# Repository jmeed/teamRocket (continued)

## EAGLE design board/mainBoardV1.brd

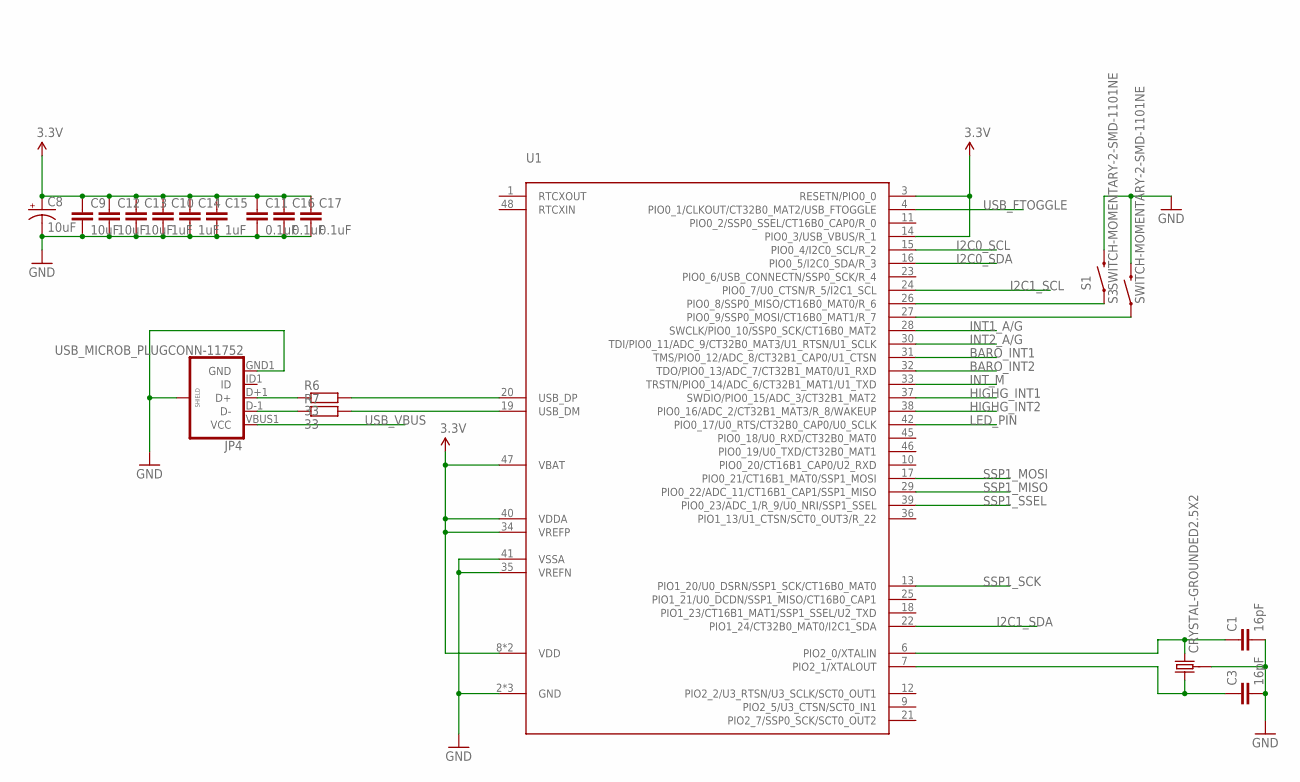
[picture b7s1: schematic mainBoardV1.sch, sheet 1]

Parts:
C1, C3: 16pF; C0402
C8: 10uF; CT3216
C9, C12, C13: 10uF; C0402
C10, C14, C15: 1uF; C0402
C11, C16, C17: 0.1uF; C0402
JP4: USB_MICROB_PLUGCONN-11752; USB-B-MICRO-SMD_V03
R6, R7: 33; R0402
S1, S3: SWITCH-MOMENTARY-2-SMD-1101NE; TACTILE-SWITCH-1101NE
U1: LPC11U68JBD48; LQFP48
U$5: CRYSTAL-GROUNDED2.5X2; CRYSTAL-SMD-2.5X2

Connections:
3.3V: C8.A (+), C9.1, C10.1, C11.1, C12.1, C13.1, C14.1, C15.1, C16.1, C17.1, U1.3 (RESETN/PIO0_0), U1.8 (VDD), U1.14 (PIO0_3/USB_VBUS/R_1), U1.34 (VREFP), U1.40 (VDDA), U1.44 (VDD), U1.47 (VBAT); also elsewhere on the board
BARO_INT1: U1.31 (TMS/PIO0_12/ADC_8/CT32B1_CAP0/U1_CTSN); also elsewhere on the board
BARO_INT2: U1.32 (TDO/PIO0_13/ADC_7/CT32B1_MAT0/U1_RXD); also elsewhere on the board
GND: C1.2, C3.2, C8.C (-), C9.2, C10.2, C11.2, C12.2, C13.2, C14.2, C15.2, C16.2, C17.2, JP4.GND1 (GND), JP4.SHIELD1 (SHIELD), JP4.SHIELD2 (SHIELD), JP4.SHIELD3 (SHIELD), S1.2, S3.2, U1.2 (GND), U1.5 (GND), U1.35 (VREFN), U1.41 (VSSA), U1.43 (GND), U$5.GND1 (3), U$5.GND2 (3); also elsewhere on the board
HIGHG_INT1: U1.37 (SWDIO/PIO0_15/ADC_3/CT32B1_MAT2); also elsewhere on the board
HIGHG_INT2: U1.38 (PIO0_16/ADC_2/CT32B1_MAT3/R_8/WAKEUP); also elsewhere on the board
I2C0_SCL: U1.15 (PIO0_4/I2C0_SCL/R_2); also elsewhere on the board
I2C0_SDA: U1.16 (PIO0_5/I2C0_SDA/R_3); also elsewhere on the board
I2C1_SCL: U1.24 (PIO0_7/U0_CTSN/R_5/I2C1_SCL); also elsewhere on the board
I2C1_SDA: U1.22 (PIO1_24/CT32B0_MAT0/I2C1_SDA); also elsewhere on the board
INT1_A/G: U1.28 (SWCLK/PIO0_10/SSP0_SCK/CT16B0_MAT2); also elsewhere on the board
INT2_A/G: U1.30 (TDI/PIO0_11/ADC_9/CT32B0_MAT3/U1_RTSN/U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); also elsewhere on the board
INT_M: U1.33 (TRSTN/PIO0_14/ADC_6/CT32B1_MAT1/U1_TXD); also elsewhere on the board
LED_PIN: U1.42 (PIO0_17/U0_RTS/CT32B0_CAP0/U0_SCLK); also elsewhere on the board
unnamed: C3.1, U1.7 (PIO2_1/XTALOUT), U$5.P1 (1)
unnamed: C1.1, U1.6 (PIO2_0/XTALIN), U$5.P2 (2)
unnamed: R6.2, U1.20 (USB_DP)
unnamed: JP4.D+1 (D+), R6.1
unnamed: JP4.D-1 (D-), R7.1
unnamed: R7.2, U1.19 (USB_DM)
unnamed: S3.1, U1.27 (PIO0_9/SSP0_MOSI/CT16B0_MAT1/R_7)
unnamed: S1.1, U1.26 (PIO0_8/SSP0_MISO/CT16B0_MAT0/R_6)
SSP1_MISO: U1.29 (PIO0_22/ADC_11/CT16B1_CAP1/SSP1_MISO); also elsewhere on the board
SSP1_MOSI: U1.17 (PIO0_21/CT16B1_MAT0/SSP1_MOSI); also elsewhere on the board
SSP1_SCK: U1.13 (PIO1_20/U0_DSRN/SSP1_SCK/CT16B0_MAT0); also elsewhere on the board
SSP1_SSEL: U1.39 (PIO0_23/ADC_1/R_9/U0_NRI/SSP1_SSEL); also elsewhere on the board
USB_FTOGGLE: U1.4 (PIO0_1/CLKOUT/CT32B0_MAT2/USB_FTOGGLE); also elsewhere on the board
USB_VBUS: JP4.VBUS1 (VCC); also elsewhere on the board

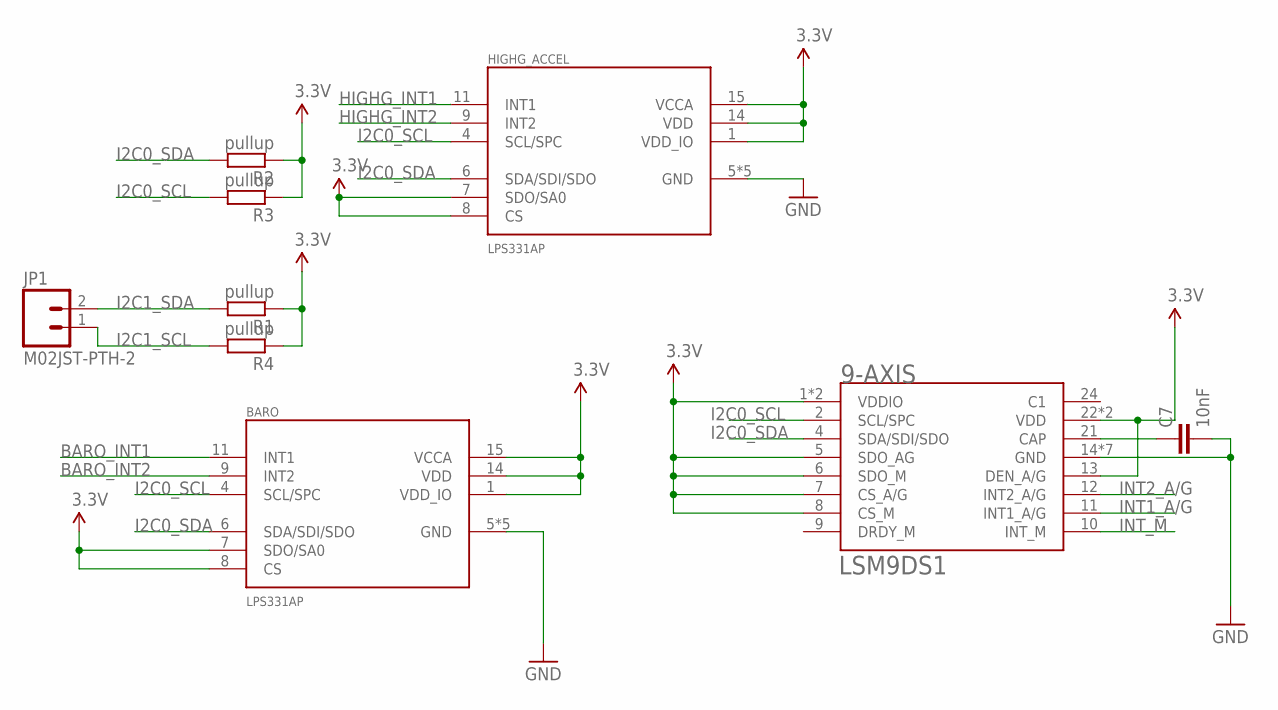
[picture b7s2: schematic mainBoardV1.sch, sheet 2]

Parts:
9-AXIS: LSM9DS1; LGA-24L-3.5X3X1
BARO: LPS331AP; LGA-16-3X3X1
C7: 10nF; C0402
HIGHG_ACCEL: LPS331AP; LGA-16-3X3X1
JP1: M02JST-PTH-2; JST-2-PTH
R1, R2, R3, R4: pullup; R0402

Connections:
3.3V: 9-AXIS.1 (VDDIO), 9-AXIS.3 (VDDIO), 9-AXIS.5 (SDO_AG), 9-AXIS.6 (SDO_M), 9-AXIS.7 (CS_A/G), 9-AXIS.8 (CS_M), 9-AXIS.13 (DEN_A/G), 9-AXIS.22 (VDD), 9-AXIS.23 (VDD), BARO.1 (VDD_IO), BARO.7 (SDO/SA0), BARO.8 (CS), BARO.14 (VDD), BARO.15 (VCCA), HIGHG_ACCEL.1 (VDD_IO), HIGHG_ACCEL.7 (SDO/SA0), HIGHG_ACCEL.8 (CS), HIGHG_ACCEL.14 (VDD), HIGHG_ACCEL.15 (VCCA), R1.1, R2.1, R3.1, R4.1; also elsewhere on the board
BARO_INT1: BARO.11 (INT1); also elsewhere on the board
BARO_INT2: BARO.9 (INT2); also elsewhere on the board
GND: 9-AXIS.14 (GND), 9-AXIS.15 (GND), 9-AXIS.16 (GND), 9-AXIS.17 (GND), 9-AXIS.18 (GND), 9-AXIS.19 (GND), 9-AXIS.20 (GND), BARO.5 (GND), BARO.10 (GND), BARO.12 (GND), BARO.13 (GND), BARO.16 (GND), C7.2, HIGHG_ACCEL.5 (GND), HIGHG_ACCEL.10 (GND), HIGHG_ACCEL.12 (GND), HIGHG_ACCEL.13 (GND), HIGHG_ACCEL.16 (GND); also elsewhere on the board
HIGHG_INT1: HIGHG_ACCEL.11 (INT1); also elsewhere on the board
HIGHG_INT2: HIGHG_ACCEL.9 (INT2); also elsewhere on the board
I2C0_SCL: 9-AXIS.2 (SCL/SPC), BARO.4 (SCL/SPC), HIGHG_ACCEL.4 (SCL/SPC), R3.2; also elsewhere on the board
I2C0_SDA: 9-AXIS.4 (SDA/SDI/SDO), BARO.6 (SDA/SDI/SDO), HIGHG_ACCEL.6 (SDA/SDI/SDO), R2.2; also elsewhere on the board
I2C1_SCL: JP1.1, R4.2; also elsewhere on the board
I2C1_SDA: JP1.2, R1.2; also elsewhere on the board
INT1_A/G: 9-AXIS.11 (INT1_A/G); also elsewhere on the board
INT2_A/G: 9-AXIS.12 (INT2_A/G); also elsewhere on the board
INT_M: 9-AXIS.10 (INT_M); also elsewhere on the board
unnamed: 9-AXIS.21 (CAP), C7.1

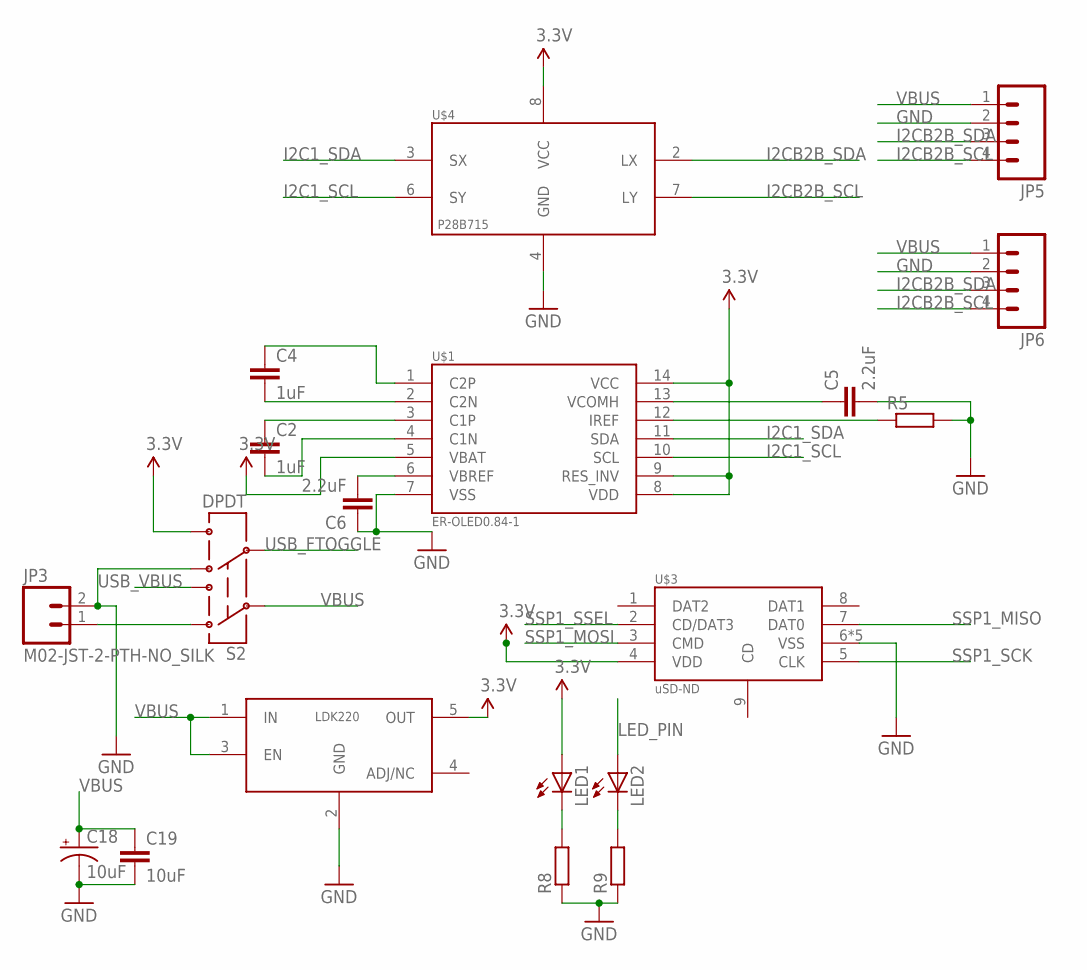
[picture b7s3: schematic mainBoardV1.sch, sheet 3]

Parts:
C2, C4: 1uF; C0402
C5, C6: 2.2uF; C0402
C18: 10uF; CT3216
C19: 10uF; C0402
JP3: M02-JST-2-PTH-NO_SILK; JST-2-PTH-NS
JP5, JP6: M04JST; 1X04-1.5MM_JST
LED1, LED2: LEDCHIPLED_0603; CHIPLED_0603
R5, R8, R9: R0402
S2: DPDT; AYZ0202
U$1: ER-OLED0.84-1; MOLEX_52892-1433
U$2: LDK220M33R; SOT23-5
U$3: MICROSD-CD; MOLEX_SD-47352-101
U$4: P82B715; SO8

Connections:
3.3V: LED1.A, S2.6, U$1.5 (VBAT), U$1.8 (VDD), U$1.9 (RES_INV), U$1.14 (VCC), U$2.5 (OUT), U$3.4 (VDD), U$4.8 (VCC); also elsewhere on the board
GND: C5.2, C6.1, C18.C (-), C19.2, JP3.2, JP5.2, JP6.2, R5.2, R8.1, R9.1, S2.4, U$1.7 (VSS), U$2.2 (GND), U$3.6 (VSS), U$3.G1 (VSS), U$3.G2 (VSS), U$3.G3 (VSS), U$3.G4 (VSS), U$4.4 (GND); also elsewhere on the board
I2C1_SCL: U$1.10 (SCL), U$4.6 (SY); also elsewhere on the board
I2C1_SDA: U$1.11 (SDA), U$4.3 (SX); also elsewhere on the board
I2CB2B_SCL: JP5.4, JP6.4, U$4.7 (LY)
I2CB2B_SDA: JP5.3, JP6.3, U$4.2 (LX)
LED_PIN: LED2.A; also elsewhere on the board
unnamed: JP3.1, S2.1
unnamed: LED1.C, R8.2
unnamed: LED2.C, R9.2
unnamed: C4.1, U$1.1 (C2P)
unnamed: C4.2, U$1.2 (C2N)
unnamed: C2.1, U$1.3 (C1P)
unnamed: C2.2, U$1.4 (C1N)
unnamed: C5.1, U$1.13 (VCOMH)
unnamed: R5.1, U$1.12 (IREF)
unnamed: C6.2, U$1.6 (VBREF)
SSP1_MISO: U$3.7 (DAT0); also elsewhere on the board
SSP1_MOSI: U$3.3 (CMD); also elsewhere on the board
SSP1_SCK: U$3.5 (CLK); also elsewhere on the board
SSP1_SSEL: U$3.2 (CD/DAT3); also elsewhere on the board
USB_FTOGGLE: S2.5; also elsewhere on the board
USB_VBUS: S2.3; also elsewhere on the board
VBUS: C18.A (+), C19.1, JP5.1, JP6.1, S2.2, U$2.1 (IN), U$2.3 (EN)

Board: 4 copper layers, 47 parts (6 on the bottom side), 42 nets, no tracks yet.

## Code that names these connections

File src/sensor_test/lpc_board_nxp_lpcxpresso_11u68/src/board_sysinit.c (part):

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STATIC const PINMUX_GRP_T pinmuxing[] = {
	/* LPCXpresso pin			- Base board function		- Mapped function */
	/* RESET-PIO0_0				- PIO/RESET (pin 4)			- Reset */
	/* PIO0_1-ISP_EN			- PIO (pin 51)				- GPIO input */
	/* PIO0_2-SSP0_SSEL			- PIO/SSEL (pin 8)			- GPIO output for SSP0 CS */
	/* PIO0_3-VBUS				-                           - USB VBUS */
	{0, 3,  (IOCON_FUNC1 | IOCON_MODE_INACT | IOCON_DIGMODE_EN)},
	/* PIO0_4-I2C_SCL			- PIO/I2C-SCL (pin 41)		- I2C0 SCL */
	{0, 4,  (IOCON_FUNC1 | IOCON_MODE_INACT | IOCON_DIGMODE_EN)},
	/* PIO0_5-I2C_SDA			- PIO/I2C-SDA (pin 40)		- I2C0 SDA */
	{0, 5,  (IOCON_FUNC1 | IOCON_MODE_INACT | IOCON_DIGMODE_EN)},
	/* PIO0_6					-                           - GPIO */
	/* PIO0_7					- PIO (pin 11)				- GPIO */
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	/* PIO1_10					- PIO (pin 49)				- GPIO */
	/* PIO1_11-I2C1_SCL			-                           - I2C1 SCL */
	{1, 11, (IOCON_FUNC1 | IOCON_MODE_INACT | IOCON_DIGMODE_EN)},
	/* PIO1_12					- PIO/USB_VBUS (pin 39)		- GPIO input */
	/* PIO1_13					- PIO (pin 38)				- GPIO output */
	/* PIO1_14-I2C_SDA			-                           - I2C SDA */
	{1, 14, (IOCON_FUNC1 | IOCON_MODE_INACT | IOCON_DIGMODE_EN)},
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
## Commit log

2014-09-15 Initial Commit with sparkfun and LPC1114 eagle libraries
2014-09-15 added eagle 6.6 links
2014-09-15 Initial project file
2014-09-16 SDCard code
2014-09-17 Ghantt chart updated
2014-09-17 project update
2014-09-17 data sheets
2014-09-20 added libary for STM32F0F0 and various ST Micro components
2014-09-21 Sensors Packages
2014-09-22 cleaned up some packages for sensors, started on main board
2014-09-26 first go at sensor interface
2014-09-26 open source for parrot, from makers of raven
2014-09-28 New sensors WIP
2014-09-28 LSM9DS1 Done
2014-09-28 molex drawings
2014-09-28 initial board + LPC MCU
2014-09-28 all major components on board, we have very little space
2014-09-29 board schematic ready for design review
2014-09-29 changed set_modet to take void*
2014-09-30 added a bunch of library files and docs
2014-10-01 up to date board, some changes are still need in schemetic
2014-10-01 Update project gantt chart to reflect current progress
2014-10-03 latest work
2014-10-03 reorged into project
    added gitattributes to treat eagle files as binaries.
2014-10-05 Board layout done with autorouting
2014-10-05 I2C guidelines documentation from NXP
2014-10-05 Updated sensors to satisfy clearance = 7mil
2014-10-05 updated pads
2014-10-05 added ThinMan basic board
2014-10-06 Removed Thumbs.db and ignore in future
2014-10-06 Routed all. Fixed USB connectivity Issue; Pending Crystal check up/power checkup
2014-10-10 gui layout prototype
2014-10-13 config file writing implemented, need to clean up code
2014-10-14 Create L3G.h
    for Pololu breakout
    set up for arduino, using Wire.h and math.h
2014-10-14 adding pololu files
2014-10-15 porting barometer arduino library, moved files around for naming conflicts
2014-10-15 more cleanup, most of LPS ported, need i2c comms
2014-10-15 added i2c libraries, replaced arduino wire with i2c in baro code
2014-10-17 prototype gyro library fixed up for i2c/base class
2014-10-17 half of accel header
2014-10-17 Project progress updates
2014-10-17 all 3 breakout libraries ported, may need to recheck i2c
2014-10-19 forgot what changes
2014-10-19 uhh don't remember this
2014-10-19 IMU library, cant test for compiler errors b/c of mising lib
2014-10-19 switched enums for #defines
2014-10-20 start main.c for freeRTOS tasks
2014-10-20 updated sensors started on thinman v2 ;
2014-10-21 added i2c_test_project, compiles if set up properly. README incoming
2014-10-21 added README for i2c_test_project
2014-10-21 small lib fixes, start on high-g lib
2014-10-21 more lib fixups for IDE testing
2014-10-21 FreeRTOS blinky. UART0 has deadlock on multi-threaded write
2014-10-21 ready to test lib with new i2c library
2014-10-21 done with high-g library
2014-10-21 forgot to remove a private i2c member from old lib
2014-10-21 fixed some more i2c stuff
2014-10-21 syntax
2014-10-21 Adding LPC libraires for 11u68 and the demo board
2014-10-21 Fixed UART0 interleaving issue. Turned out to be another stack overflow
2014-10-23 removed old broken 4088 project
2014-10-23 added working i2c c file for 11u68
2014-10-23 thinManV2 changes
2014-10-23 test commit
2014-10-23 fixed i2c.c to not overwrite the txBuff when rxBuff is retrieved
2014-10-24 working neopixel code close #6
2014-10-24 lib changes to proper i2c library
2014-10-24 sensor testing project, .c i2c works but .cpp i2c does not
2014-10-24 C version librarys of pololu sensors
2014-10-24 calibration change
2014-10-24 Xpresso code ready to test, fixed compile errors in clibs
2014-10-24 working project with sensor libraries, demoable
2014-10-24 whoops, didn't include it
2014-10-24 changed thinman sensor libs to C language
2014-10-24 being ocd about variable placement
2014-10-24 debugged compile errors for thinman sensors
2014-10-25 FreeRTOS SPI code in testing
2014-10-25 SDHC works on init
2014-10-25 Comprehensive SD012 support (untested for 01)
2014-10-25 SDCard Simple Read (sector 0) Works
2014-10-26 Create TinyGPS.cpp
    http://arduiniana.org/libraries/tinygps/
2014-10-26 Create TinyGPS.h
    http://arduiniana.org/libraries/tinygps/
2014-10-27 moved Parrot to ref, added dir for TinyGPS in ref
2014-10-29 SDCard DiskIO
2014-10-31 updated thinManV2 and lipoWing to use 0603 parts
2014-11-01 finished schematic for telemetryWing
2014-11-01 telemtry board done
2014-11-01 telemtryWing moved board edge down a bit
2014-11-01 fixed LPS lib for LPS331, IMU talks but reads 0
2014-11-01 added scienceWing
2014-11-02 main.c changes
2014-11-03 LPS331 baro and LSMD9S1 imu, aka final sensors, talking correctly, albeit noisy
2014-11-03 sampling rate adjustments for accel
2014-11-03 Firing Board
2014-11-03 deleted: firing.sch
2014-11-03 boards shipped
2014-11-03 Fixed connection for ISP power source
2014-11-04 added connectWings
2014-11-06 Working Thinman #1 SDCard Write
2014-11-06 Working SDCard Logging
2014-11-06 Sensor test
2014-11-09 More logging. Fixed SDCard Logging Race condition (caused corruption etc)
2014-11-10 Fixed all fatfs race conditions by incorporating mutxes in fatfs (reentrant option)
2014-11-10 Janky Baro + IMU reading
2014-11-10 Quad Testing data
2014-11-10 Mathematica sketchpad for test launch
2014-11-10 removed some files, lots of changes to main.c, main.c should be able to run on thinman
2014-11-12 Routing Firing Board
2014-11-12 Altium PDF generation job
2014-11-12 Fixed known DRC by adding 3D models where appropriate
2014-11-12 flash library implemented need to test reading
2014-11-12 fixed reading/writing
2014-11-12 few typos in flash
2014-11-12 Fixed 13mil annular ring. AVRISP 3D model for clearance check
2014-11-12 Fixed Power annular rings
2014-11-12 Fixed all annular ring issues
2014-11-12 Tented susceptible vias
2014-11-13 Fixed cosmetics and high power annular ring (to 10mil)
2014-11-16 matlab-xbee example
2014-11-16 xbee serial setup
2014-11-16 xbee ground station code
2014-11-16 no clue what this changed
2014-11-16 Cproject
2014-11-17 added bluetooth test code for arduino
2014-11-17 turned on magnetometer logging
2014-11-17 USB UART
2014-11-18 added flight test data
2014-11-19 Thinman v2. Tested flash sector write
2014-11-19 Janky working thinman V2 flash
2014-11-20 Something weird
2014-11-20 Testing
2014-11-21 A few changes
2014-11-21 Firing board output settings update
2014-11-22 minor fixes
2014-11-22 2 ground stations: one will attempt real time visualization, one will log and visualize after the fact
2014-11-22 filtering code in C, started on xbee task setup
2014-11-23 Working SDCard logging with Baro only
2014-11-24 filtering code on thinman
2014-11-24 storing gyro values for xbee use
2014-11-24 Working H3L
2014-11-24 typos and missing defs
2014-11-24 RB USART0
2014-11-24 Testing RN4020
2014-11-24 Working Bluetooth binding
2014-11-25 Janky bluetooth handling
2014-11-25 I2C1 test code
2014-11-29 firing board driver
2014-11-29 BOM output on firing board
2014-11-29 Blocking neopixel
2014-11-30 Voltage recording and firing
2014-12-01 Simple I2C UART tester; Firing board depleted charge detecter
2014-12-01 Revert "USB UART"
    This reverts commit e38d26ed90174e369b38e323cf258aebb3d6a3a3.
    Removing USB code from thinmanV1 for safety reasons
2014-12-01 matlab post processing for altitude, duration, thrust time, peak accel, avg accel. needs IMU and BARO files
2014-12-01 Fixed sensor codes
2014-12-01 Flight code
2014-12-01 Flight 3 data
2014-12-02 calc_stats tweak from new launch
2014-12-02 orientation tracking station for xbee station
2014-12-03 FreeRTOS update 8.0
2014-12-03 added semi-working android application
2014-12-03 fixing comment issue in redlib_stubs.c
2014-12-03 Extra logging
2014-12-03 Fixed up i2c_uart driver to standard; IMU over xbee
2014-12-03 interface comments
2014-12-03 deleted an autosave, small merge
2014-12-03 removed gps transmit, got tracker working-ish with awful parsing
2014-12-03 adding additional commands for bluetooth_command
2014-12-04 added current altitude to fld response over bluetooth
2014-12-04 Fixed XBee output
2014-12-04 small tweaks to tracker
2014-12-04 modifying order of bluetooth response for flight data - also simple filter on altitude and crude speed calculation
2014-12-04 fixed stupid mistake with array indices
2014-12-04 a super duper important space
2014-12-04 Hot swap external boards
2014-12-04 added in status functionality, not tested
2014-12-04 working app
2014-12-04 Fixed small bug in app
2014-12-04 NEMA xbee
2014-12-04 Firing
2014-12-04 Fixed status issue
2014-12-04 Fixed connected textview on status screen
2014-12-06 Fix for status sending over bt
2014-12-06 Fix for shitty SD cards
2014-12-06 FreeRTOS GPS log buffering; XBee test log (computer side)
2014-12-06 AVR fix NEOPixel timing issue in a unsuccessful cooperative interrupt enable scheme from Polulu?; added GPIO pull-down for Telem wing; added stack to vFlushLogs due to observed stack overflow conditi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
2014-12-06 Firing BOM and out job setting for getting the BOM file generated
2014-12-09 Corrected reversed voltage divider on sense channels
2014-12-09 New comments
2014-12-25 removed .key file
